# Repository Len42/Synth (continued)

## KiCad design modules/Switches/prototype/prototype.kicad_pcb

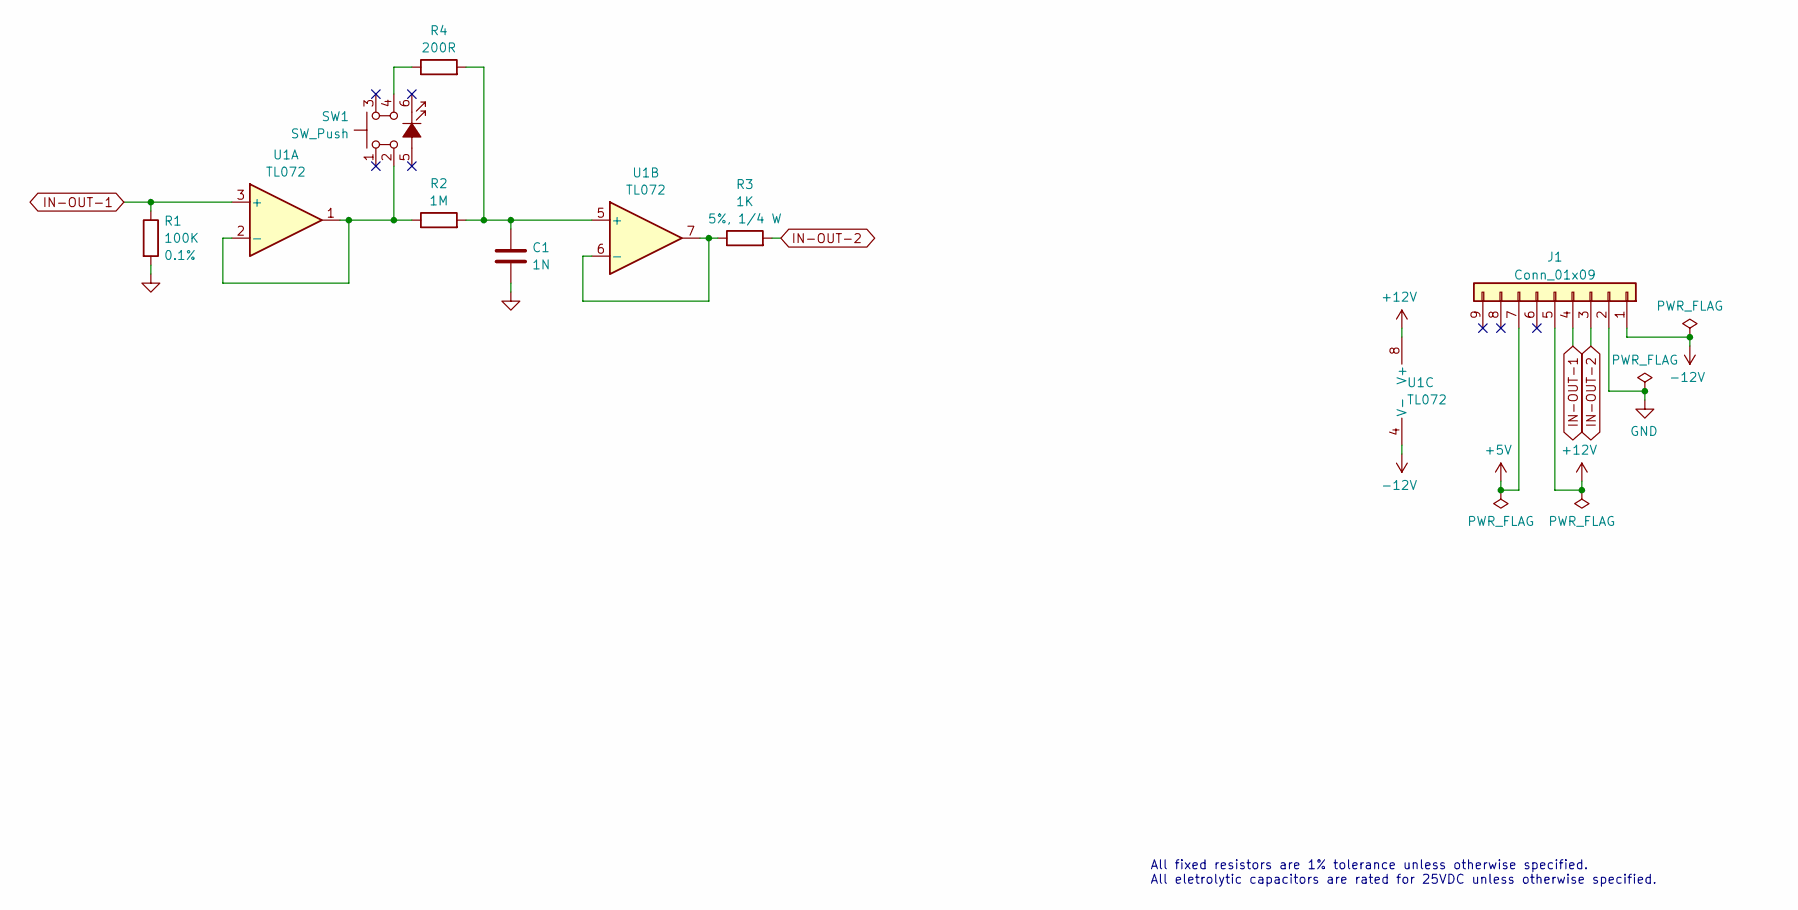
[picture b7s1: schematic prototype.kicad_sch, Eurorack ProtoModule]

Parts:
C1: 1N; C_Rect_Kemet_L7.2mm_W2.5mm_P5mm
J1: Conn_01x09; PinHeader_1x09_P2.54mm_Vertical
R1: 100K; SB_Gen_1; ManufacturerPartNum RN55C1003BRE6
R2: 1M; R_Axial_DIN0207_L6.3mm_D2.5mm_P7.62mm_Horizontal; ManufacturerPartNum MFR-12*
R3: 1K; SB_Gen_3; ManufacturerPartNum CCF071K00JKE36
R4: 200R; SB_Gen_1; ManufacturerPartNum MFR-12*
SW1: SW_Push; SW_Push_LED_C&K_D6R; ManufacturerPartNum D6RLBUF1 LFS
U1: TL072; DIP-8_W7.62mm; ManufacturerPartNum TL072BCP

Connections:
+5V: J1.7
+12V: J1.5, U1.8 (V+)
-12V: J1.1, U1.4 (V-)
GND: C1.2, J1.2, R1.2
IN-OUT-1: J1.4, R1.1, U1.3 (+)
IN-OUT-2: J1.3, R3.2
unnamed: R4.1, SW1.4
unnamed: R2.1, SW1.2, U1.1, U1.2 (-)
unnamed: C1.1, R2.2, R4.2, U1.5 (+)
unnamed: R3.1, U1.6 (-), U1.7

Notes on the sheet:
All fixed resistors are 1% tolerance unless otherwise specified. All eletrolytic capacitors are rated for 25VDC unless otherwise specified.

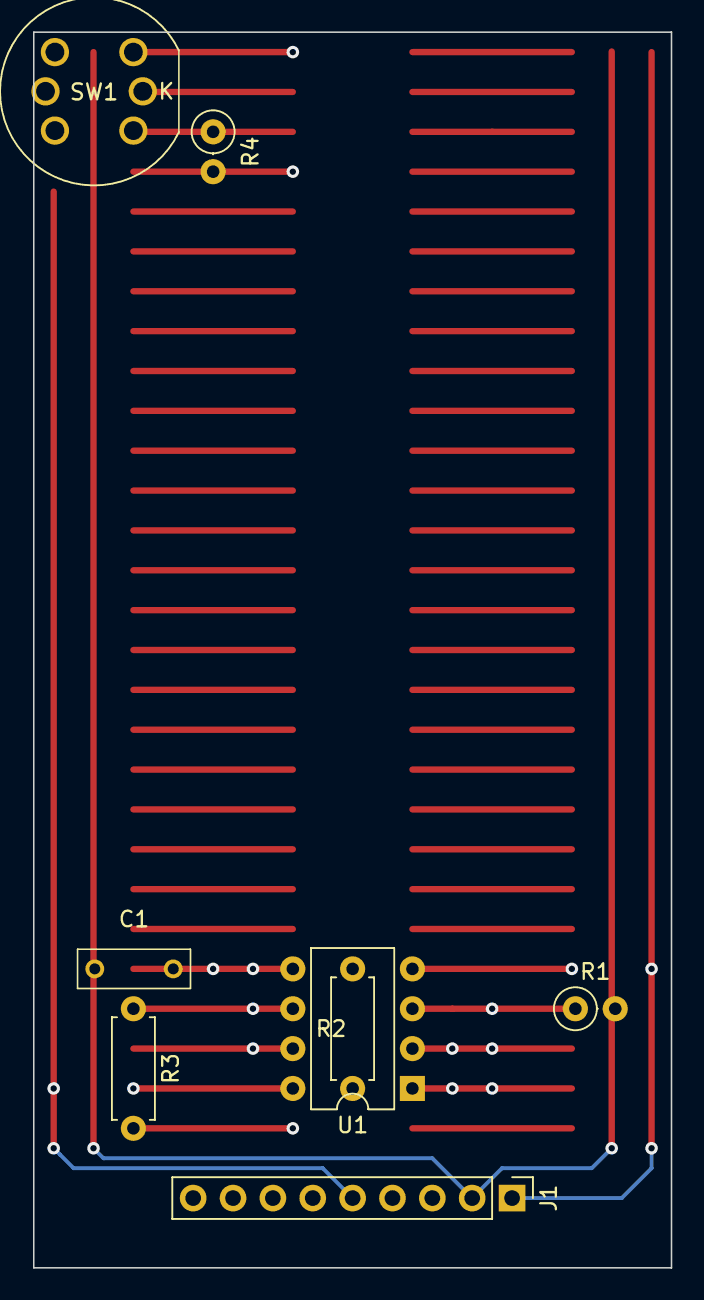
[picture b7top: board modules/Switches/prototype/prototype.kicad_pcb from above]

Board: 6 copper layers, 40.6 x 78.7 mm, 8 parts (0 on the bottom side), 9 nets.
